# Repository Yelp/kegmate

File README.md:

# KegMate

KegMate includes
[KegBoard](http://github.com/Yelp/kegmate/tree/master/KegBoard/), an
[Arduino kegbot firmware](http://kegbot.org) and board layout, to our
[KegPad](http://github.com/Yelp/kegmate/tree/master/KegPad/), iPad app.

For more information on Kegbot see [KegBot.org](http://kegbot.org).

For more information see the [Wiki](http://wiki.github.com/Yelp/kegmate/).

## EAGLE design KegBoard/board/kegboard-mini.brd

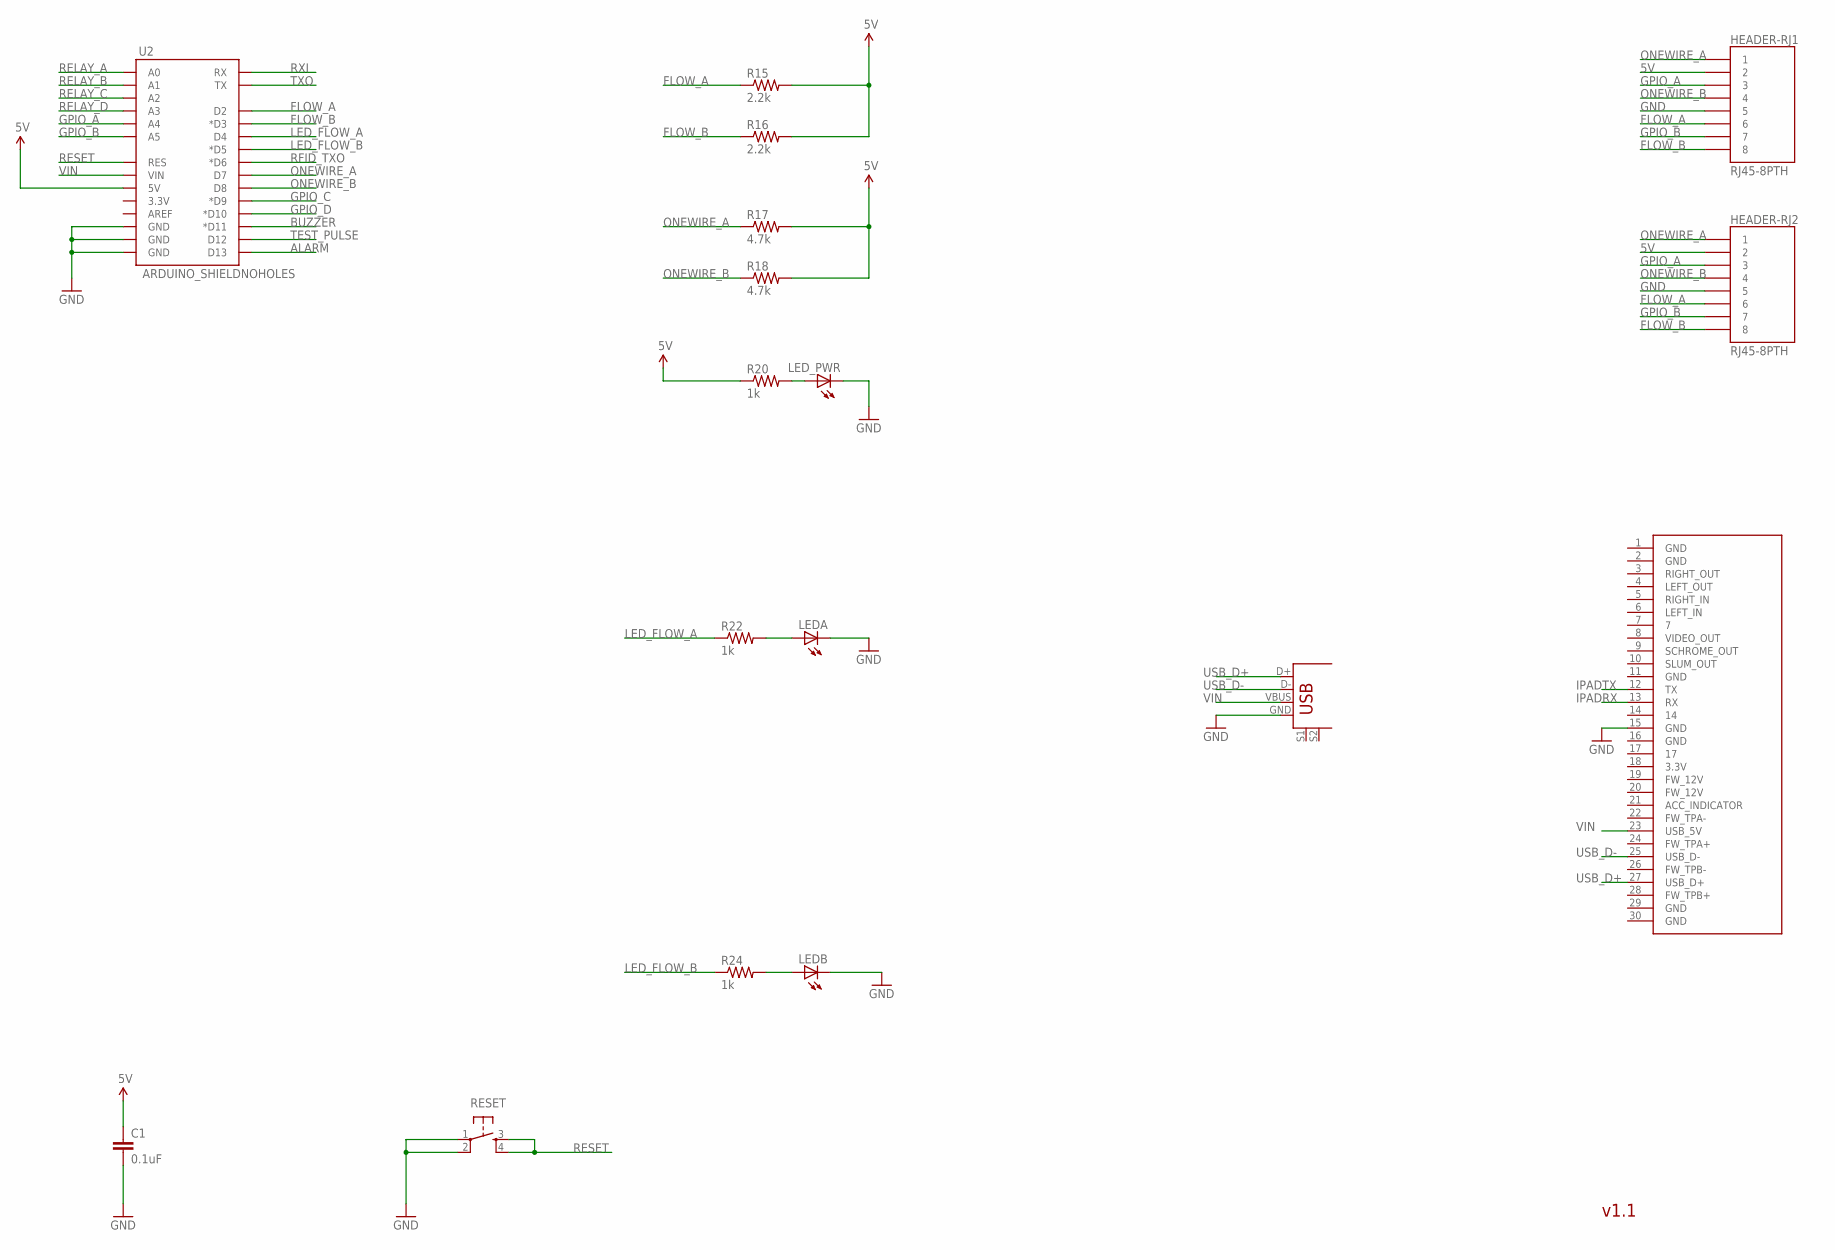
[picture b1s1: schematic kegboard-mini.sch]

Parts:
C1: 0.1uF; CAP-PTH-SMALL
HEADER-RJ1, HEADER-RJ2: RJ45-8PTH; RJ45-8
LEDA: LED3MM
LEDB: LED3MM
LED_PWR: LED3MM
R15, R16: 2.2k; AXIAL-0.3
R17, R18: 4.7k; AXIAL-0.3
R20, R22, R24: 1k; AXIAL-0.3
RESET: TAC_SWITCHPTH; TACTILE-PTH
U2: ARDUINO_SHIELDNOHOLES; DUEMILANOVE_SHIELD_NOHOLES
U$2: USB+SHIELD; USB-B-PTH
U$19: IPOD_CONNECTOR_MALE; IPOD_MALE_CONNECTOR

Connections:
5V: C1.1, HEADER-RJ1.2, HEADER-RJ2.2, R15.P$2 (2), R16.P$2 (2), R17.P$2 (2), R18.P$2 (2), R20.P$1 (1), U2.5V
ALARM: U2.D13
BUZZER: U2.D11 (*D11)
FLOW_A: HEADER-RJ1.6, HEADER-RJ2.6, R15.P$1 (1), U2.D2
FLOW_B: HEADER-RJ1.8, HEADER-RJ2.8, R16.P$1 (1), U2.D3 (*D3)
GND: C1.2, HEADER-RJ1.5, HEADER-RJ2.5, LEDB.K (C), LED_PWR.K (C), RESET.1, RESET.2, U2.GND@0 (GND), U2.GND@1 (GND), U2.GND@2 (GND), U$2.GND, U$19.15 (GND)
GPIO_A: HEADER-RJ1.3, HEADER-RJ2.3, U2.A4
GPIO_B: HEADER-RJ1.7, HEADER-RJ2.7, U2.A5
GPIO_C: U2.D9 (*D9)
GPIO_D: U2.D10 (*D10)
IPADRX: U$19.13 (RX)
IPADTX: U$19.12 (TX)
LED_FLOW_A: R22.P$1 (1), U2.D4
LED_FLOW_B: R24.P$1 (1), U2.D5 (*D5)
unnamed: LEDA.A, R22.P$2 (2)
unnamed: LEDB.A, R24.P$2 (2)
unnamed: LED_PWR.A, R20.P$2 (2)
ONEWIRE_A: HEADER-RJ1.1, HEADER-RJ2.1, R17.P$1 (1), U2.D7
ONEWIRE_B: HEADER-RJ1.4, HEADER-RJ2.4, R18.P$1 (1), U2.D8
RELAY_A: U2.A0
RELAY_B: U2.A1
RELAY_C: U2.A2
RELAY_D: U2.A3
RESET: RESET.3, RESET.4, U2.RES
RFID_TXO: U2.D6 (*D6)
RXI: U2.RX
TEST_PULSE: U2.D12
TXO: U2.TX
USB_D+: U$2.D+, U$19.27 (USB_D+)
USB_D-: U$2.D-, U$19.25 (USB_D-)
VIN: U2.VIN, U$2.VBUS, U$19.23 (USB_5V)

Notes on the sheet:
v1.1

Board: 2 copper layers, 22 parts (0 on the bottom side), 17 nets, no tracks yet.

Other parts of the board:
JP1, JP2, JP3, JP4, JP5: STAND-OFF

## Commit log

2010-08-10 Importing
2010-08-10 Moving iPad KegBot to iKegBot; Updating README
2010-08-10 Revert "Moving iPad KegBot to iKegBot; Updating README"
    This reverts commit 6dda33c06cd6b2c4e34068a47167db4b23849e20.
2010-08-10 Updatings docs
2010-08-11 Renaming KegBot to KegMate; Renaming iPad app to KegPad
2010-08-11 Updated docs
2010-08-11 Renaming KegBot proj to KegPad.
2010-08-26 Updating to use YAJL iOS framework
2010-09-28 HID ProxPoint Plus support for arduino. This is a little hacky, but works!
2010-09-28 HID ProxCard support in KegPad. Also, added CRC checking to packets, rearranged some code.
2010-09-28 Login updates; Moving simulator
2010-09-28 Sign up and user login scaffolds
2010-09-29 Sign up forms
2010-09-29 Updating data store and KBUser
2010-09-29 README
2010-10-01 Small change to enable onewire temp sensor.
2010-10-01 Admin interface for adding users, beers and kegs.
2010-10-01 Created PCInterrupt handler for generic handling of PCInterrupts. Modified MagStripe to use this code.
2010-10-01 Using GHKit framework.
2010-10-02 Updating GHKit framework
2010-10-02 Hack to fix pouring. Adding Pranqster image. Fixing beer type label width.
2010-10-06 Fixing user edit. Doing basic validation.
2010-10-08 Rating UI and persistence. Activity prevents log out and short timer delay before logout after pour.
2010-10-10 Script to convert card ids to the same format as output by HID reader.
2010-10-12 Admin and display fixes; Temp guage fix. Ratings fixes. Bug fixes.
2010-10-13 Rating (chalk) view; Renaming KBKegProcessor; Log out in user edit; Admin/Status buttons
2010-10-13 Re-adding / improving support for the ID12 HID reader. We can now run both the HID reader and the ID12 reader at the same time.
2010-10-14 Literboard fixes
2010-10-14 Flow meter on status page.
2010-10-14 Chart view
2010-10-14 Minor updates to keg processing.
2010-10-14 Making beer video loop
2010-10-18 Not saving keg temperature (Until we figure out whats killing the core data store.
2010-10-18 A couple more beers
2010-10-18 Adding deploy script to deploy builds to all kegmates via scp
2010-10-18 Keg admin; Adding more beers; Making chart view 6 hours; Fixing for long beer names and descriptions.
2010-10-18 Flip fix; Admin fixture always loads
2010-10-18 Fixing chart time index
2010-10-18 Adding debug output from the flow meter. Adding a new beer.
2010-10-18 Adding Lagunitas IPA
2010-10-19 Adding a couple more beers.
2010-10-29 Updating kegboard messages to store a timestamp that starts as soon as we start to parse the message.
2010-10-30 Adding a few more beers. Hopefully fixing bad first pours.
2010-11-06 Making leaderboard daily; Fixing form constructor initing.
2010-11-18 Admin fixes; Cascade delete rule on some models
2010-12-03 Adding support for adding beer image from photo library.
2010-12-03 Updates to image selection
2010-12-03 Adding samichlaus
2011-02-06 Some beer and DB processing scripts
2011-02-08 Setting keg when creating new keg
2011-02-08 Dismissing image popover on use. Fixing (null) google image search.
2011-02-09 adding serpents stout
2011-02-09 WIP beer search (prepping for lots of beers)
2011-02-18 Adding license file
2011-05-11 Admin login (password).
    Twitter connect and sharing of pours
    (experimental!).
    Updated YAJL and GHKit.
    If you pour within 30 seconds as same user, it
    adds to previous pour.
    Fixing docs.
2011-05-15 More twitter sharing, admin login fixes, about screen.
2011-05-15 Adding name for KegPad so they can all use the same twitter account
2011-05-15 Fixing some build warnings and updating docs
2011-06-05 Updating install docs
2011-06-19 update Permissions doc in markdown
2011-07-18 Updating .gitignore for xcode4
2011-07-18 Updating KegPad to use latest kegboard protocol. Updating Kegboard with latest merged kegbot code.
2011-07-21 Adding settings for tweet for anonymous pour and max pour amount.
2011-07-22 Removing unsupported fonts HelveticaNeue-UltraLight and HelveticaNeue-Light
2011-07-28 Prototype for loading kegs in admin from kegbot api
2011-07-28 Generating all the KegBot API objects as RKManagedObjects.
2011-07-29 Working support for posting temperatures, drinks, reading beers, reading kegs
2011-07-29 Fix errant ifdef
2011-08-02 further api support work
2011-08-03 KegTime
2011-08-03 KegTime tweaks
2011-08-03 Adding kegboard config for SF
2011-08-09 Manually enter a KegTimeHost and connect.
2011-08-14 KegTime fixes
2011-08-15 Removing userdata
2011-08-15 Trying to add support for remote and self views and I've got some funny GL problems. Not ready yet.
2011-08-29 Fixing viewing self
2011-08-30 More WIP
2011-09-08 Fixing build for mobile kegmates
2012-01-31 Fixing script for new schema
2012-09-27 Updating sf hardware config
2012-09-27 WIP on creating a kegmate-specific pcb layout

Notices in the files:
parts and their libraries:
SparkFun-Connectors: Licensing: CC v3.0 Share-Alike You are welcome to use this library for commercial purposes.
